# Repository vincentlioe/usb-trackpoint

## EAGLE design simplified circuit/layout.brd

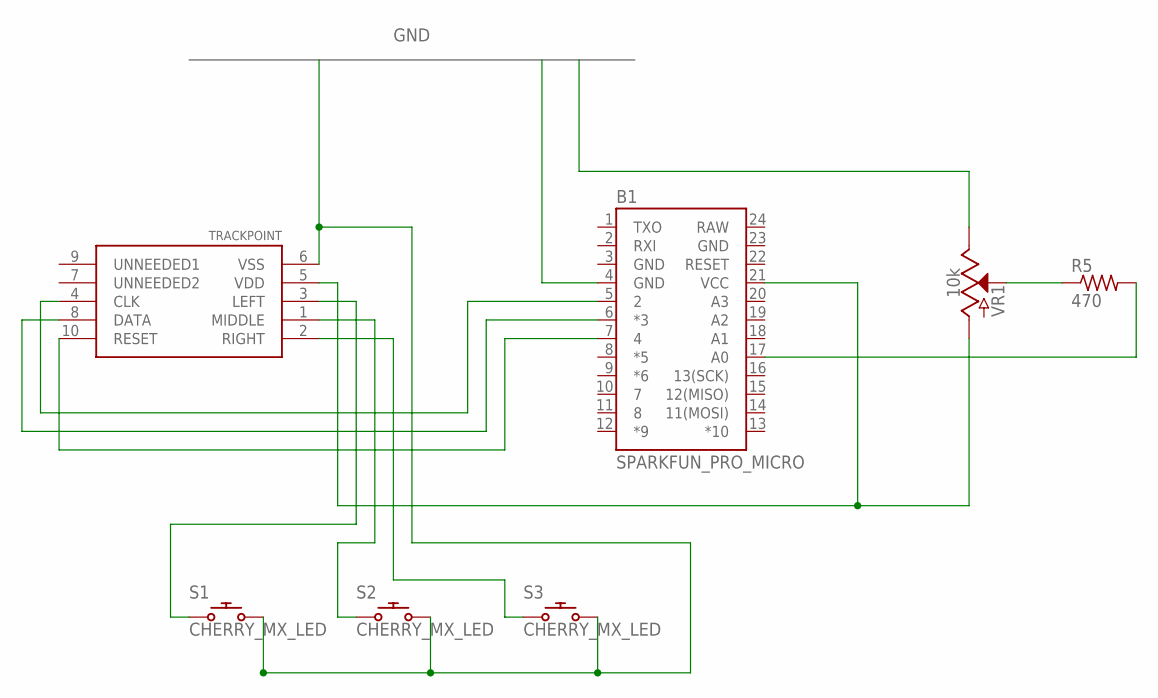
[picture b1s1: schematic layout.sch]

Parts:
B1: SPARKFUN_PRO_MICRO
R5: 470; 0207/10
S1, S2, S3: CHERRY_MX_LED
TRACKPOINT: BOARD
VR1: 10k; POT-PTH-ALPS-KIT

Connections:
GND: B1.3 (GND), B1.4 (GND), B1.23 (GND), S1.S2 (2), S2.S2 (2), S3.S2 (2), TRACKPOINT.6 (VSS), VR1.P$1 (E)
unnamed: B1.6 (*3), TRACKPOINT.8 (DATA)
unnamed: B1.7 (4), TRACKPOINT.10 (RESET)
unnamed: B1.5 (2), TRACKPOINT.4 (CLK)
unnamed: R5.1, VR1.P$2 (S)
unnamed: B1.17 (A0), R5.2
unnamed: S1.S1 (1), TRACKPOINT.3 (LEFT)
unnamed: S2.S1 (1), TRACKPOINT.1 (MIDDLE)
unnamed: S3.S1 (1), TRACKPOINT.2 (RIGHT)
unnamed: B1.21 (VCC), TRACKPOINT.5 (VDD), VR1.P$3 (A)
RAW: B1.24 (RAW)

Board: 2 copper layers, 7 parts (1 on the bottom side), 10 nets, no tracks yet.

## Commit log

2020-08-28 fork initial commit added simplified circuit for arduino pro micro leonardo and x240 trackpoint

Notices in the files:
parts and their libraries:
SparkFun-Boards: Licensing: Creative Commons ShareAlike 4.0 International - https://creativecommons.org/licenses/by-sa/4.0
